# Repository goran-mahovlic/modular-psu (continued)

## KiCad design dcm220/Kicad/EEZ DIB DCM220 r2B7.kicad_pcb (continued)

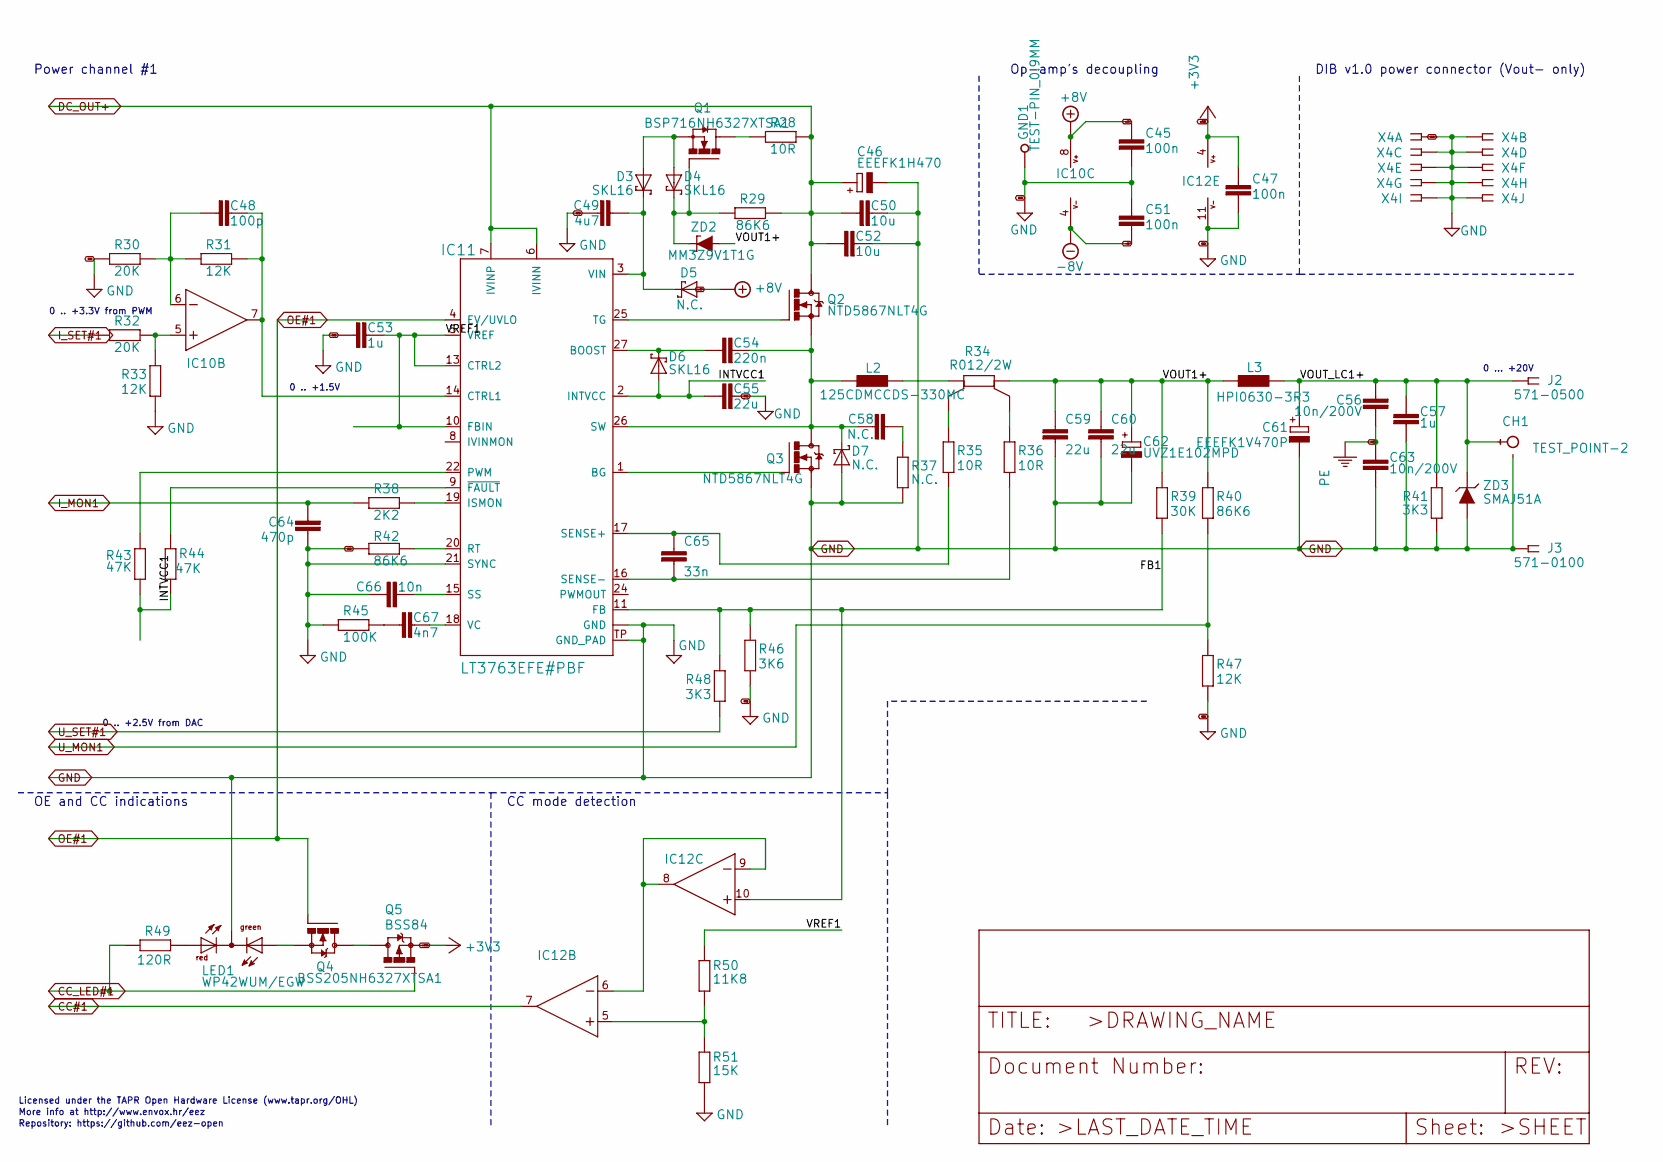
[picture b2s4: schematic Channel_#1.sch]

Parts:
C45, C47, C51: 100n; C0603
C46: EEEFK1H470; CAPAE830X1050N
C48: 100p; C0805
C49: 4u7; C1206
C50, C52: 10u; C1210
C53, C57: 1u; C0805
C54: 220n; C0805
C55: 22u; C1206
C56, C63: 10n/200V; C1206
C58: N.C.; C0805
C59, C60: 22u; C1210
C61: EEEFK1V470P; CAPAE660X610N
C62: UVZ1E102MPD; ECAP5_10.5
C64: 470p; C0805
C65: 33n; C0805
C66: 10n; C0805
C67: 4n7; C0805
CH1: TEST_POINT-2; TP_1.1MM_2
D3, D4, D6: SKL16; SOD123
D5: N.C.; SOD123
D7: N.C.; SMA
GND: TEST-PIN_0.9MM
IC10: MC33272ADR2G; SOIC127P600X173-8N
IC11: LT3763EFE#PBF; LTC_05-08-1663-EB
IC12: MC33274ADR2G; SOIC127P600X175-14N
J2: 571-0500; DELTRON_571
J3: 571-0100; DELTRON_571
L2: 125CDMCCDS-330MC; 125CDMCC_DS
L3: HPI0630-3R3; COILCRAFT_HPI0630
LED1: WP42WUM/EGW; L-42WUM-1EGWT
Q1: BSP716NH6327XTSA1; SOT223
Q2, Q3: NTD5867NLT4G; TO229P990X239-3N
Q4: BSS205NH6327XTSA1; SOT103P240X110-3N
Q5: BSS84; SOT95P237X112-3N
R28, R35, R36: 10R; R0805
R29, R40, R42: 86K6; R0805
R30, R32: 20K; R0805
R31, R33, R47: 12K; R0805
R34: R012/2W; R_2512-4WIRE
R37: N.C.; R1206
R38: 2K2; R0805
R39: 30K; R0805
R41, R48: 3K3; R0805
R43, R44: 47K; R0805
R45: 100K; R0805
R46: 3K6; R0805
R49: 120R; R0805
R50: 11K8; R0805
R51: 15K; R0805
X4: DS1024-2*5R0; SSW-105-02-T-D-RA
ZD2: MM3Z9V1T1G; SOD323-W
ZD3: SMAJ51A; DO214AA

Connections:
/Channel #1/FB1: IC11.11 (FB), IC12.10 (+IN), R39.1, R46.2, R48.2
/Channel #1/INTVCC1: C55.1, D6.A, IC11.2 (INTVCC), R43.1, R44.2
/Channel #1/VOUT1+: C59.1, C60.1, C62.+, L3.1, R34.2, R39.2, R40.2, ZD2.A
/Channel #1/VOUT_LC1+: C56.2, C57.1, C61.1 (+), CH1.TIP, J2.1, J2.1.1, L3.2, R41.1, ZD3.C
/Channel #1/VREF1: C53.1, IC11.5 (VREF), IC11.10 (FBIN), IC11.13 (CTRL2), R50.2
CC#1: IC12.7 (OUT); also elsewhere on the board
CC_LED#1: Q5.1 (G), R49.2; also elsewhere on the board
DC_OUT+: C46.+, C50.1, C52.1, IC11.6 (IVINN), IC11.7 (IVINP), Q2.2 (D), R28.1, R29.1; also elsewhere on the board
I_MON1: C64.2, R38.1; also elsewhere on the board
I_SET#1: R32.1; also elsewhere on the board
unnamed: C48.1, IC10.7 (OUT), IC11.14 (CTRL1), R31.2
unnamed: C48.2, IC10.6 (-IN), R30.2, R31.1
unnamed: C49.1, D3.C, D5.C, IC11.3 (VIN)
unnamed: C54.1, D6.C, IC11.27 (BOOST)
unnamed: C54.2, C58.1, D7.C, IC11.26 (SW), L2.1, Q2.3 (S), Q3.2 (D)
unnamed: C58.2, R37.2
unnamed: C65.1, IC11.17 (SENSE+), R35.1
unnamed: C65.2, IC11.16 (SENSE-), R36.1
unnamed: C66.2, IC11.15 (SS)
unnamed: C67.1, R45.2
unnamed: C67.2, IC11.18 (VC)
unnamed: D3.A, D4.A, Q1.3 (S)
unnamed: D4.C, Q1.1 (G), R29.2, ZD2.C
unnamed: IC10.5 (+IN), R32.2, R33.2
unnamed: IC11.1 (BG), Q3.1 (G)
unnamed: IC11.9 (~FAULT), R44.1
unnamed: IC11.19 (ISMON), R38.2
unnamed: IC11.20 (RT), R42.2
unnamed: IC11.22 (PWM), R43.2
unnamed: IC11.25 (TG), Q2.1 (G)
unnamed: IC12.5 (+IN), R50.1, R51.2
unnamed: IC12.6 (-IN), IC12.8 (OUT), IC12.9 (-IN)
unnamed: L2.2, R34.1
unnamed: LED1.GREEN (AG), Q4.2 (S)
unnamed: LED1.RED (AR), R49.1
unnamed: Q1.2 (D), Q1.4 (D), R28.2
unnamed: Q4.3 (D), Q5.3 (D)
unnamed: R34.1S, R35.2
unnamed: R34.2S, R36.2
OE#1: IC11.4 (EV/UVLO), Q4.1 (G); also elsewhere on the board
PE: C56.1, C63.1; also elsewhere on the board
U_MON1: R40.1, R47.2; also elsewhere on the board
U_SET#1: R48.1; also elsewhere on the board

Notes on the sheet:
Licensed under the TAPR Open Hardware License (www.tapr.org/OHL)
Repository: https://github.com/eez-open
More info at http://www.envox.hr/eez
0 ... +20V
0 .. +3.3V from PWM
0 .. +1.5V
0 .. +2.5V from DAC
Power channel #1
CC mode detection
DIB v1.0 power connector (Vout- only)
Op-amp's decoupling
OE and CC indications

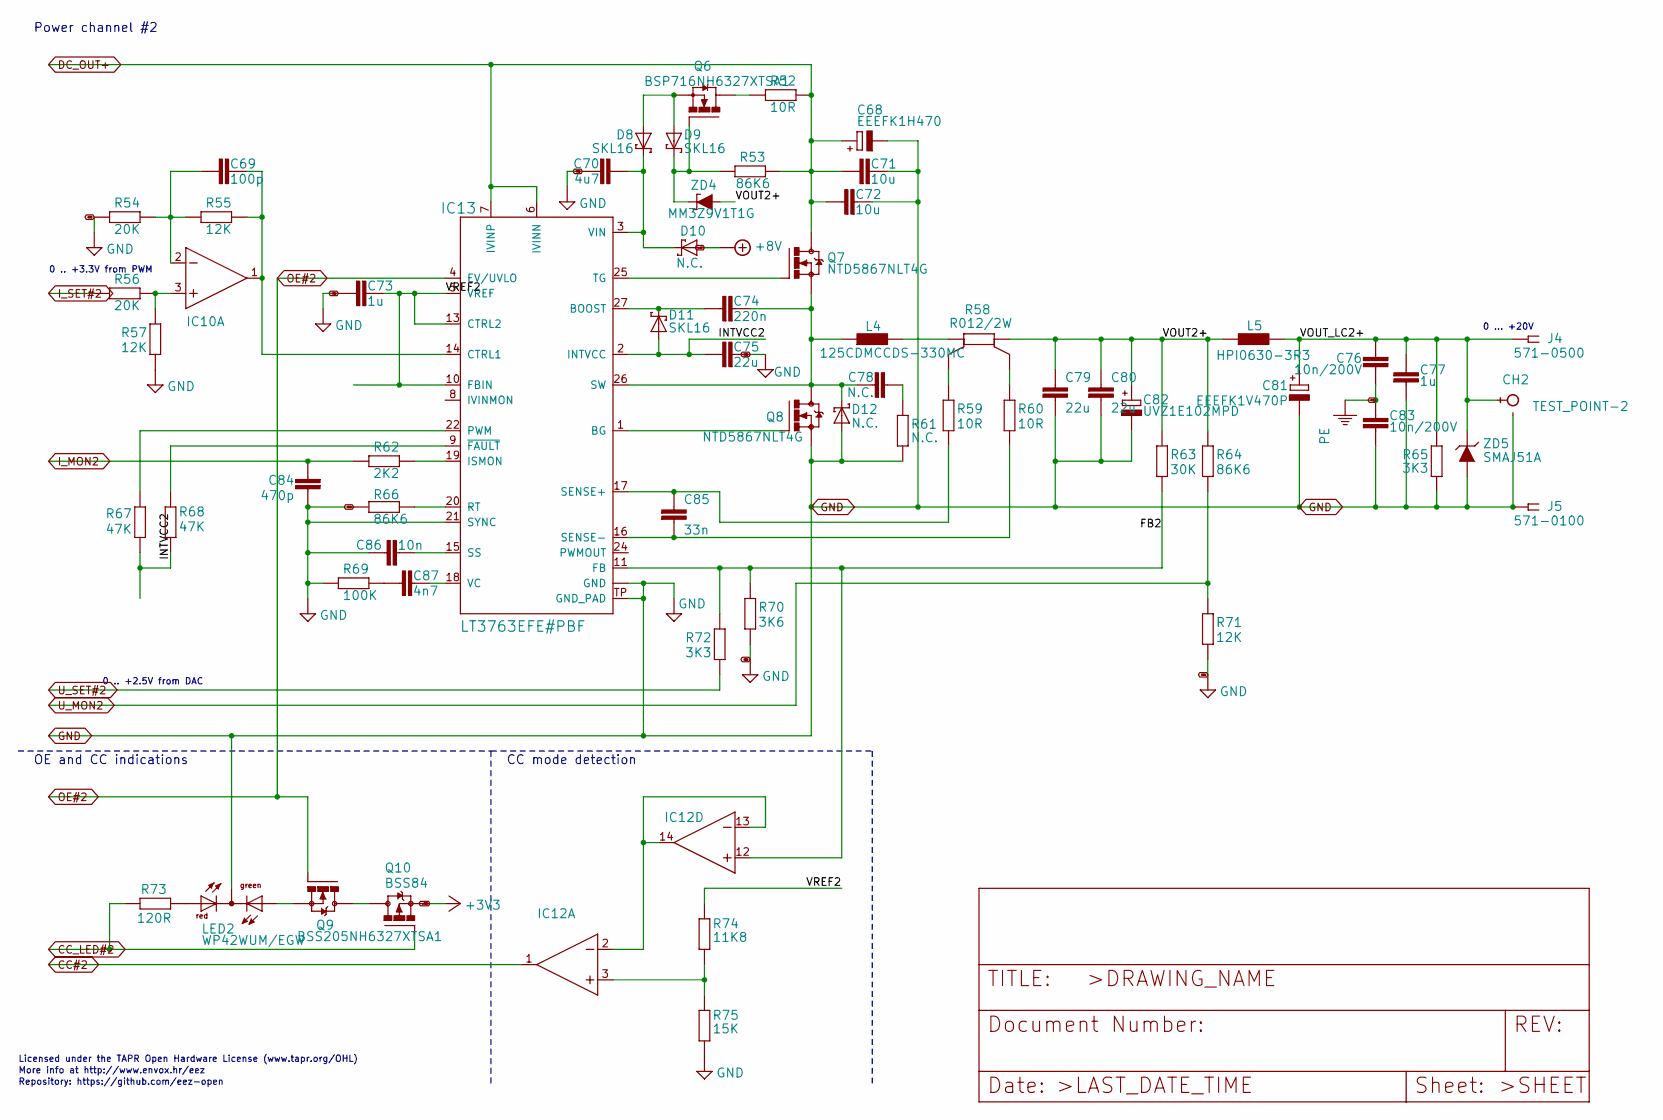
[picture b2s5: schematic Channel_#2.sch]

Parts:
C68: EEEFK1H470; CAPAE830X1050N
C69: 100p; C0805
C70: 4u7; C1206
C71, C72: 10u; C1210
C73, C77: 1u; C0805
C74: 220n; C0805
C75: 22u; C1206
C76, C83: 10n/200V; C1206
C78: N.C.; C0805
C79, C80: 22u; C1210
C81: EEEFK1V470P; CAPAE660X610N
C82: UVZ1E102MPD; ECAP5_10.5
C84: 470p; C0805
C85: 33n; C0805
C86: 10n; C0805
C87: 4n7; C0805
CH2: TEST_POINT-2; TP_1.1MM_2
D8, D9, D11: SKL16; SOD123
D10: N.C.; SOD123
D12: N.C.; SMA
IC10: MC33272ADR2G; SOIC127P600X173-8N
IC12: MC33274ADR2G; SOIC127P600X175-14N
IC13: LT3763EFE#PBF; LTC_05-08-1663-EB
J4: 571-0500; DELTRON_571
J5: 571-0100; DELTRON_571
L4: 125CDMCCDS-330MC; 125CDMCC_DS
L5: HPI0630-3R3; COILCRAFT_HPI0630
LED2: WP42WUM/EGW; L-42WUM-1EGWT
Q6: BSP716NH6327XTSA1; SOT223
Q7, Q8: NTD5867NLT4G; TO229P990X239-3N
Q9: BSS205NH6327XTSA1; SOT103P240X110-3N
Q10: BSS84; SOT95P237X112-3N
R52, R59, R60: 10R; R0805
R53, R64, R66: 86K6; R0805
R54, R56: 20K; R0805
R55, R57, R71: 12K; R0805
R58: R012/2W; R_2512-4WIRE
R61: N.C.; R1206
R62: 2K2; R0805
R63: 30K; R0805
R65, R72: 3K3; R0805
R67, R68: 47K; R0805
R69: 100K; R0805
R70: 3K6; R0805
R73: 120R; R0805
R74: 11K8; R0805
R75: 15K; R0805
ZD4: MM3Z9V1T1G; SOD323-W
ZD5: SMAJ51A; DO214AA

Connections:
/Channel #2/FB2: IC12.12 (+IN), IC13.11 (FB), R63.1, R70.2, R72.2
/Channel #2/INTVCC2: C75.1, D11.A, IC13.2 (INTVCC), R67.1, R68.2
/Channel #2/VOUT2+: C79.1, C80.1, C82.+, L5.1, R58.2, R63.2, R64.2, ZD4.A
/Channel #2/VOUT_LC2+: C76.2, C77.1, C81.1 (+), CH2.TIP, J4.1, J4.1.1, L5.2, R65.1, ZD5.C
/Channel #2/VREF2: C73.1, IC13.5 (VREF), IC13.10 (FBIN), IC13.13 (CTRL2), R74.2
CC#2: IC12.1 (OUT); also elsewhere on the board
CC_LED#2: Q10.1 (G), R73.2; also elsewhere on the board
DC_OUT+: C68.+, C71.1, C72.1, IC13.6 (IVINN), IC13.7 (IVINP), Q7.2 (D), R52.1, R53.1; also elsewhere on the board
I_MON2: C84.2, R62.1; also elsewhere on the board
I_SET#2: R56.1; also elsewhere on the board
unnamed: C69.1, IC10.1 (OUT), IC13.14 (CTRL1), R55.2
unnamed: C69.2, IC10.2 (-IN), R54.2, R55.1
unnamed: C70.1, D8.C, D10.C, IC13.3 (VIN)
unnamed: C74.1, D11.C, IC13.27 (BOOST)
unnamed: C74.2, C78.1, D12.C, IC13.26 (SW), L4.1, Q7.3 (S), Q8.2 (D)
unnamed: C78.2, R61.2
unnamed: C85.1, IC13.17 (SENSE+), R59.1
unnamed: C85.2, IC13.16 (SENSE-), R60.1
unnamed: C86.2, IC13.15 (SS)
unnamed: C87.1, R69.2
unnamed: C87.2, IC13.18 (VC)
unnamed: D8.A, D9.A, Q6.3 (S)
unnamed: D9.C, Q6.1 (G), R53.2, ZD4.C
unnamed: IC10.3 (+IN), R56.2, R57.2
unnamed: IC12.3 (+IN), R74.1, R75.2
unnamed: IC12.2 (-IN), IC12.13 (-IN), IC12.14 (OUT)
unnamed: IC13.1 (BG), Q8.1 (G)
unnamed: IC13.9 (~FAULT), R68.1
unnamed: IC13.19 (ISMON), R62.2
unnamed: IC13.20 (RT), R66.2
unnamed: IC13.22 (PWM), R67.2
unnamed: IC13.25 (TG), Q7.1 (G)
unnamed: L4.2, R58.1
unnamed: LED2.GREEN (AG), Q9.2 (S)
unnamed: LED2.RED (AR), R73.1
unnamed: Q6.2 (D), Q6.4 (D), R52.2
unnamed: Q9.3 (D), Q10.3 (D)
unnamed: R58.1S, R59.2
unnamed: R58.2S, R60.2
OE#2: IC13.4 (EV/UVLO), Q9.1 (G); also elsewhere on the board
PE: C76.1, C83.1; also elsewhere on the board
U_MON2: R64.1, R71.2; also elsewhere on the board
U_SET#2: R72.1; also elsewhere on the board

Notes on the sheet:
Licensed under the TAPR Open Hardware License (www.tapr.org/OHL)
Repository: https://github.com/eez-open
More info at http://www.envox.hr/eez
0 ... +20V
CC mode detection
OE and CC indications
Power channel #2
0 .. +3.3V from PWM
0 .. +2.5V from DAC

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
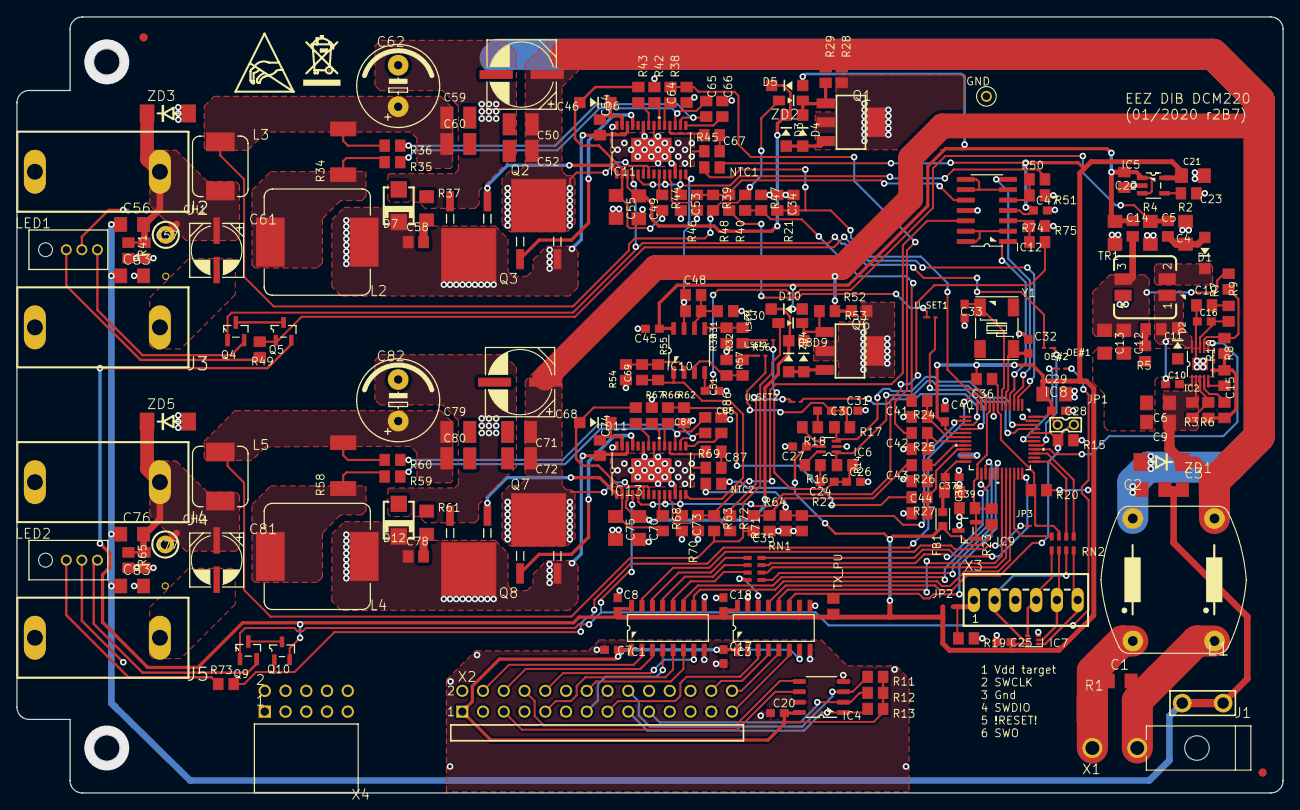
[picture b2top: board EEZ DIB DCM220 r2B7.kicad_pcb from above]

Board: 2 copper layers, 155.0 x 95.0 mm, 247 parts (0 on the bottom side), 168 nets.

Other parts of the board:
EEZ_SIGNATURE: SIGNATURESMALL; SIGNATURE_5MM
U$2: RECYCLE_BIN1_8
U$4: ESD_SYMBOL

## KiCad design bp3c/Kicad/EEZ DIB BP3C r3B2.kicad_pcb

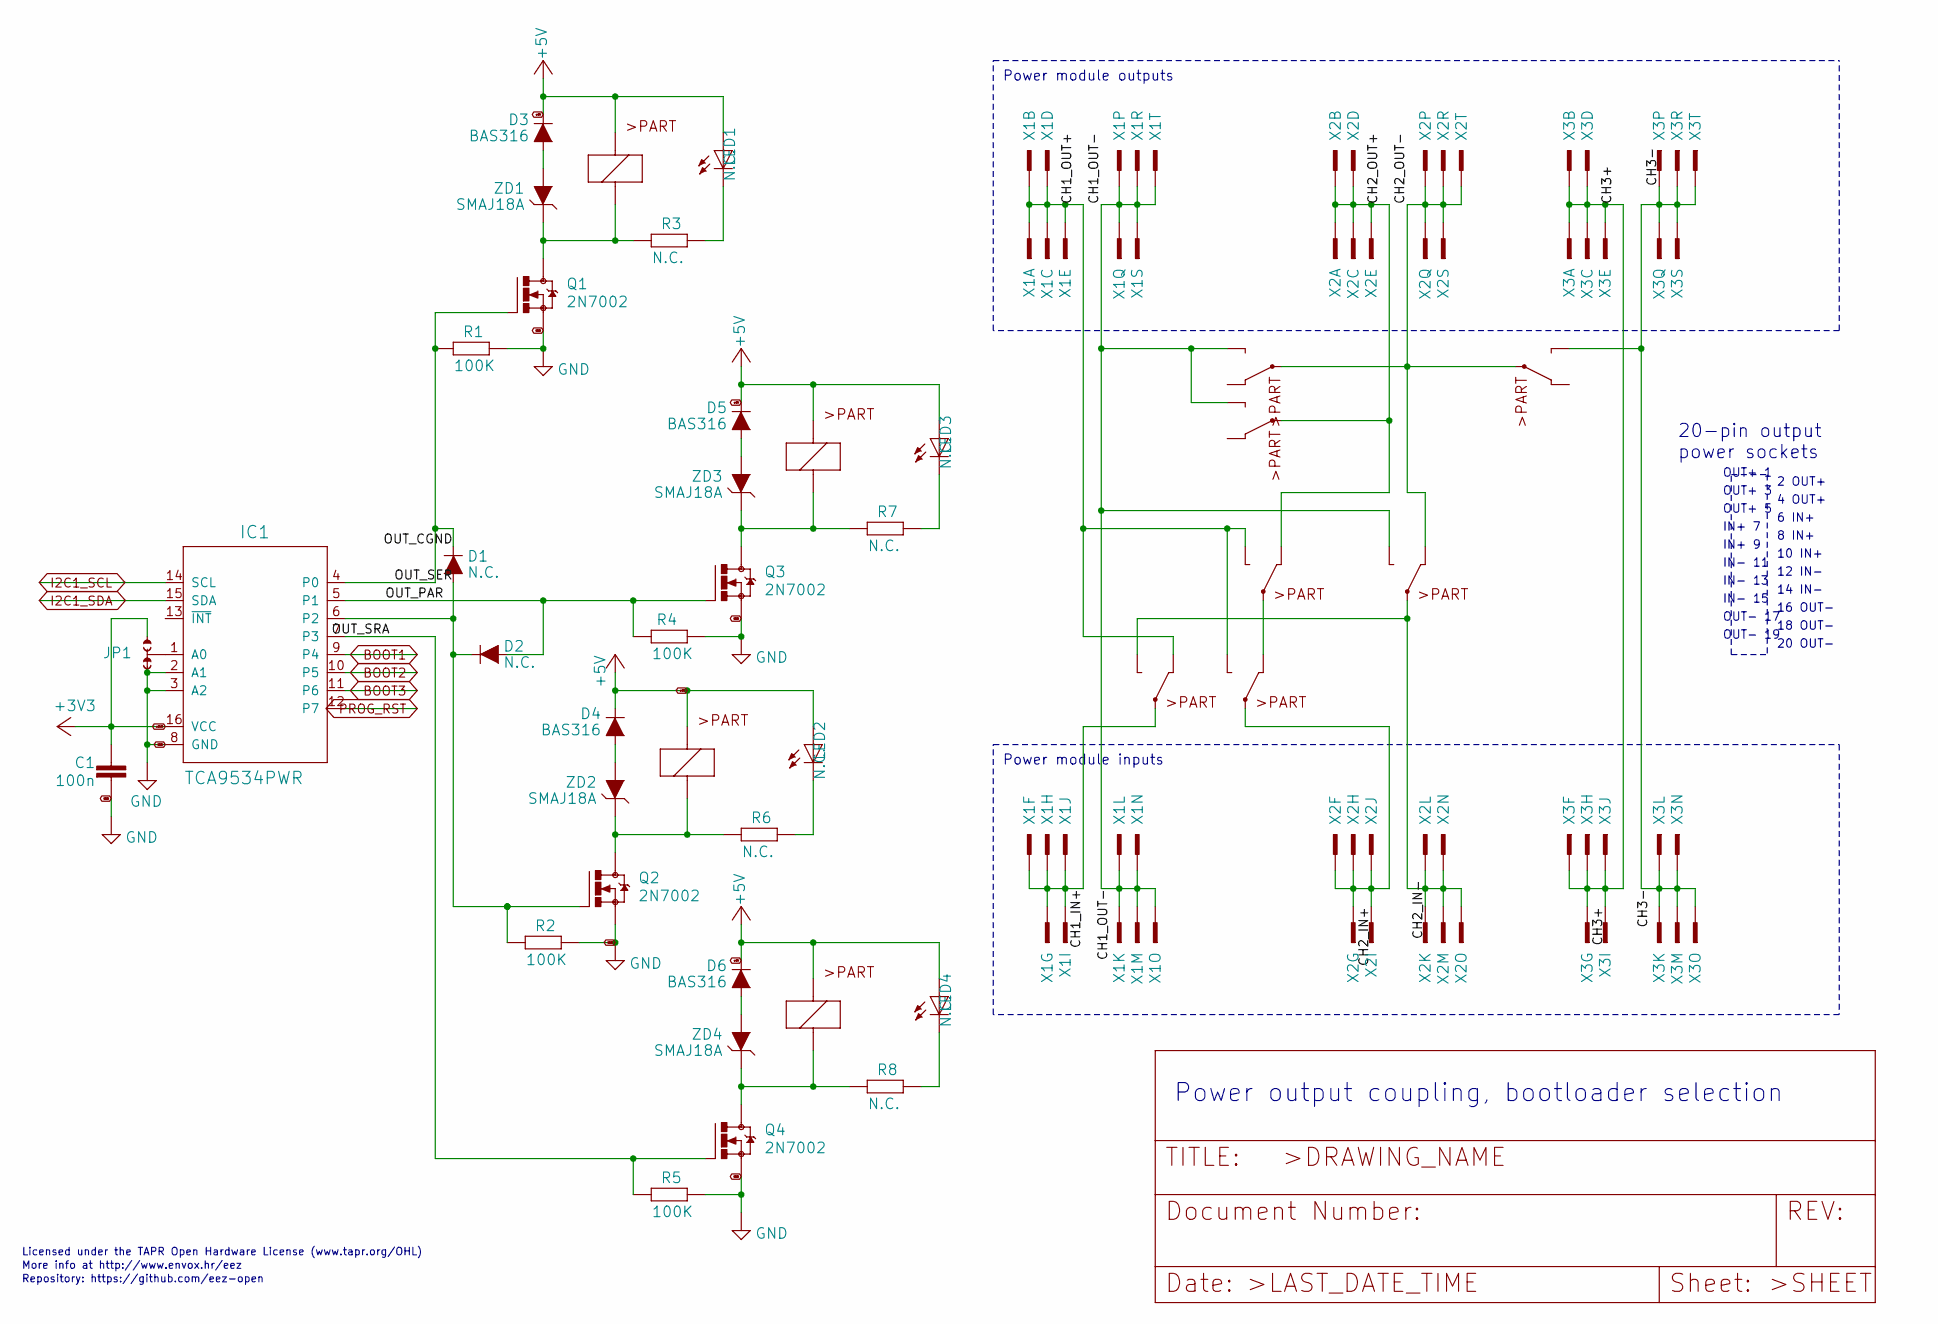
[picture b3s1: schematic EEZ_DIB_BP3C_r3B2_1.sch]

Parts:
C1: 100n; C0603
D1, D2: N.C.; SOD323-R
D3, D4, D5, D6: BAS316; SOD323-R
IC1: TCA9534PWR; PW(R-PDSO-G16)
JP1: JP3-CUT
K1, K2, K3, K4: RT424005; RT-C_016A5_ROUND
LED1, LED2, LED3, LED4: N.C.; LED_0805
Q1, Q2, Q3, Q4: 2N7002; SOT103P240X110-3N
R1, R2, R4, R5: 100K; R0805
R3, R6, R7, R8: N.C.; R0805
X1, X2, X3: ZL202-20G; DS1021-2*10SF11
ZD1, ZD2, ZD3, ZD4: SMAJ18A; DO214AC

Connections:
+3V3: C1.1, IC1.16 (VCC), JP1.NO; also elsewhere on the board
+5V: D3.C, D4.C, D5.C, D6.C, K1.A2 (C1), K2.A2 (C1), K3.A2 (C1), K4.A2 (C1), LED1.A, LED2.A, LED3.A, LED4.A; also elsewhere on the board
/EEZ DIB BP3C r3B2_1/CH1_IN+: K1.11A, X1.6, X1.7, X1.8, X1.9, X1.10
/EEZ DIB BP3C r3B2_1/CH1_OUT+: K1.12A (S), K1.14B (O), K2.14A (O), X1.1, X1.2, X1.3, X1.4, X1.5
/EEZ DIB BP3C r3B2_1/CH1_OUT-: K2.14B (O), K3.14A (O), K4.14A (O), X1.11, X1.12, X1.13, X1.14, X1.15, X1.16, X1.17, X1.18, X1.19, X1.20
/EEZ DIB BP3C r3B2_1/CH2_IN+: K1.11B, X2.6, X2.7, X2.8, X2.9, X2.10
/EEZ DIB BP3C r3B2_1/CH2_IN-: K1.14A (O), K2.11B, X2.11, X2.12, X2.13, X2.14, X2.15
/EEZ DIB BP3C r3B2_1/CH2_OUT+: K2.12A (S), K4.11A, X2.1, X2.2, X2.3, X2.4, X2.5
/EEZ DIB BP3C r3B2_1/CH2_OUT-: K2.12B (S), K3.11A, K3.11B, X2.16, X2.17, X2.18, X2.19, X2.20
/EEZ DIB BP3C r3B2_1/CH3+: X3.1, X3.2, X3.3, X3.4, X3.5, X3.6, X3.7, X3.8, X3.9, X3.10
/EEZ DIB BP3C r3B2_1/CH3-: K3.14B (O), X3.11, X3.12, X3.13, X3.14, X3.15, X3.16, X3.17, X3.18, X3.19, X3.20
/EEZ DIB BP3C r3B2_1/OUT_CGND: D1.C, IC1.4 (P0), Q1.1 (G), R1.2
/EEZ DIB BP3C r3B2_1/OUT_PAR: D2.A, IC1.5 (P1), Q3.1 (G), R4.2
/EEZ DIB BP3C r3B2_1/OUT_SER: D1.A, D2.C, IC1.6 (P2), Q2.1 (G), R2.2
/EEZ DIB BP3C r3B2_1/OUT_SRA: IC1.7 (P3), Q4.1 (G), R5.2
BOOT1: IC1.9 (P4); also elsewhere on the board
BOOT2: IC1.10 (P5); also elsewhere on the board
BOOT3: IC1.11 (P6); also elsewhere on the board
GND: C1.2, IC1.2 (A1), IC1.3 (A2), IC1.8 (GND), JP1.NC, Q1.2 (S), Q2.2 (S), Q3.2 (S), Q4.2 (S), R1.1, R2.1, R4.1, R5.1; also elsewhere on the board
I2C1_SCL: IC1.14 (SCL); also elsewhere on the board
I2C1_SDA: IC1.15 (SDA); also elsewhere on the board
unnamed: D3.A, ZD1.A
unnamed: D4.A, ZD2.A
unnamed: D5.A, ZD3.A
unnamed: D6.A, ZD4.A
unnamed: IC1.1 (A0), JP1.COM
unnamed: K1.12B (S), K2.11A
unnamed: K1.A1 (C2), Q2.3 (D), R6.2, ZD2.C
unnamed: K2.A1 (C2), Q3.3 (D), R7.2, ZD3.C
unnamed: K3.A1 (C2), Q1.3 (D), R3.2, ZD1.C
unnamed: K4.A1 (C2), Q4.3 (D), R8.2, ZD4.C
unnamed: LED1.C, R3.1
unnamed: LED2.C, R6.1
unnamed: LED3.C, R7.1
unnamed: LED4.C, R8.1
PROG_RST: IC1.12 (P7); also elsewhere on the board

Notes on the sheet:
Licensed under the TAPR Open Hardware License (www.tapr.org/OHL)
Repository: https://github.com/eez-open
More info at http://www.envox.hr/eez
Power output coupling, bootloader selection
Power module inputs
Power module outputs
IN+ 7
16 OUT-
6 IN+
20-pin output power sockets
10 IN+
IN+ 9
2 OUT+
12 IN-
OUT+ 1
IN- 11
8 IN+
OUT+ 5
OUT- 19
4 OUT+
OUT- 17
20 OUT-
OUT+ 3
14 IN-
IN- 15
IN- 13
18 OUT-

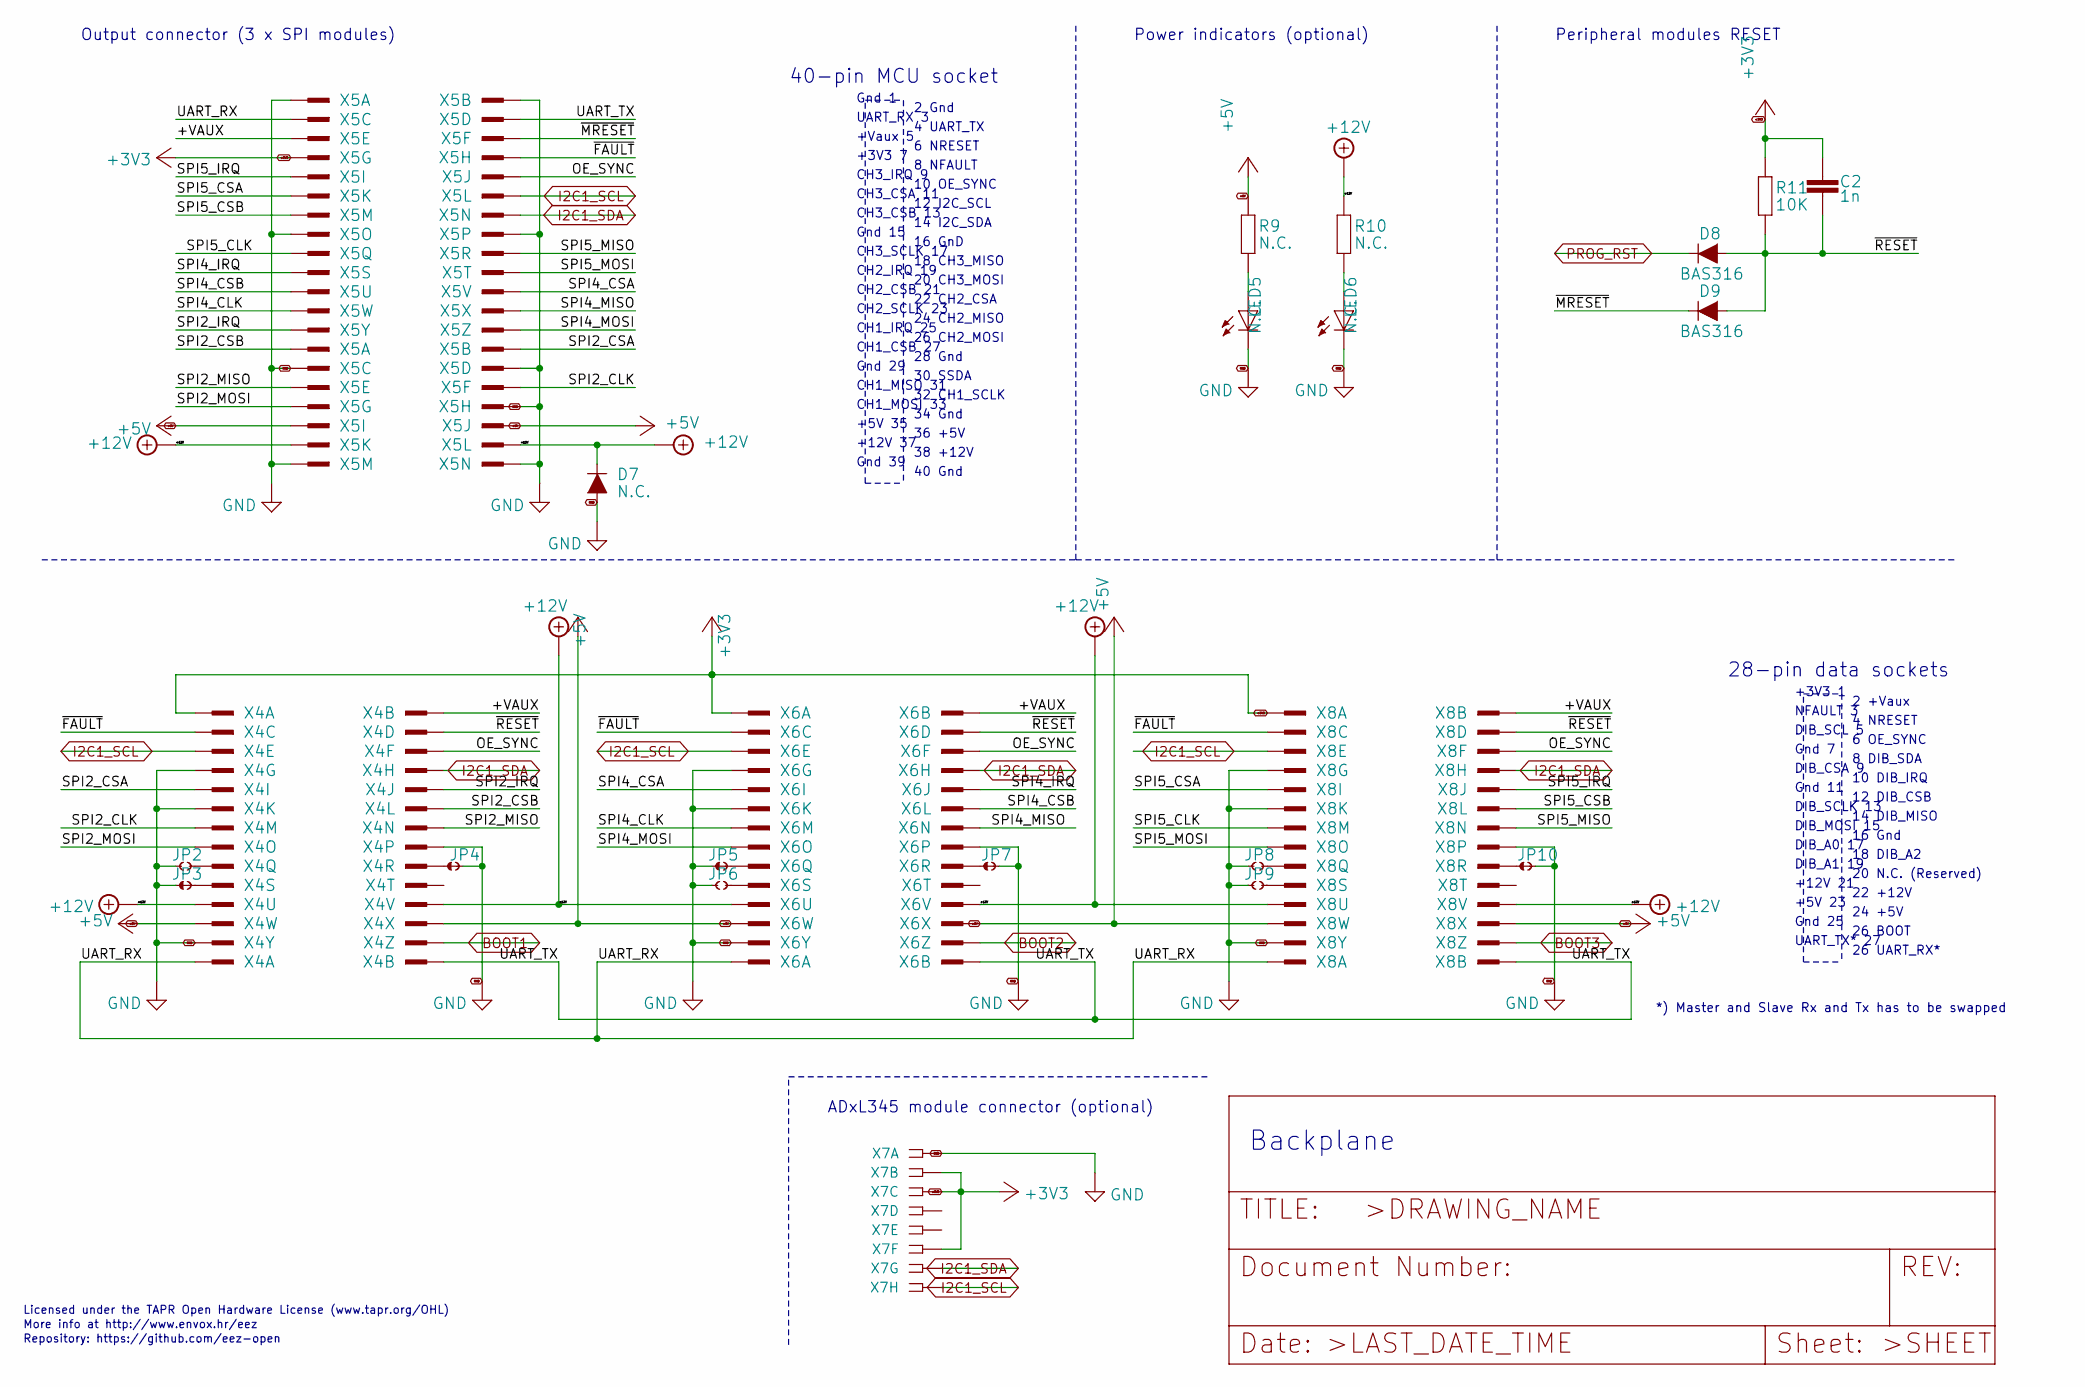
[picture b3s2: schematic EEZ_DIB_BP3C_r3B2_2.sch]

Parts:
C2: 1n; C0805
D7: N.C.; DO214AA
D8, D9: BAS316; SOD323-R
JP2, JP6, JP8, JP9: JP2-CUT
JP3, JP4, JP5, JP7, JP10: JP2-NOCUT
LED5, LED6: N.C.; LED_0805
R9, R10: N.C.; R0805
R11: 10K; R0805
X4, X6, X8: DS1023-2*14S21; TSW-114-07-F-D
X5: DS1022-2*20RF11; ZL212-40KG
X7: N.C.; SSW-108-02-S-S

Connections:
+3V3: C2.2, R11.1, X4.1, X5.7, X6.1, X7.2, X7.3, X7.6, X8.1; also elsewhere on the board
+5V: R9.1, X4.23, X4.24, X5.35, X5.36, X6.23, X6.24, X8.23, X8.24; also elsewhere on the board
+12V: D7.C, R10.1, X4.21, X4.22, X5.37, X5.38, X6.21, X6.22, X8.21, X8.22
/EEZ DIB BP3C r3B2_2/+VAUX: X4.2, X5.5, X6.2, X8.2
/EEZ DIB BP3C r3B2_2/OE_SYNC: X4.6, X5.10, X6.6, X8.6
/EEZ DIB BP3C r3B2_2/SPI2_CLK: X4.13, X5.32
/EEZ DIB BP3C r3B2_2/SPI2_CSA: X4.9, X5.28
/EEZ DIB BP3C r3B2_2/SPI2_CSB: X4.12, X5.27
/EEZ DIB BP3C r3B2_2/SPI2_IRQ: X4.10, X5.25
/EEZ DIB BP3C r3B2_2/SPI2_MISO: X4.14, X5.31
/EEZ DIB BP3C r3B2_2/SPI2_MOSI: X4.15, X5.33
/EEZ DIB BP3C r3B2_2/SPI4_CLK: X5.23, X6.13
/EEZ DIB BP3C r3B2_2/SPI4_CSA: X5.22, X6.9
/EEZ DIB BP3C r3B2_2/SPI4_CSB: X5.21, X6.12
/EEZ DIB BP3C r3B2_2/SPI4_IRQ: X5.19, X6.10
/EEZ DIB BP3C r3B2_2/SPI4_MISO: X5.24, X6.14
/EEZ DIB BP3C r3B2_2/SPI4_MOSI: X5.26, X6.15
/EEZ DIB BP3C r3B2_2/SPI5_CLK: X5.17, X8.13
/EEZ DIB BP3C r3B2_2/SPI5_CSA: X5.11, X8.9
/EEZ DIB BP3C r3B2_2/SPI5_CSB: X5.13, X8.12
/EEZ DIB BP3C r3B2_2/SPI5_IRQ: X5.9, X8.10
/EEZ DIB BP3C r3B2_2/SPI5_MISO: X5.18, X8.14
/EEZ DIB BP3C r3B2_2/SPI5_MOSI: X5.20, X8.15
/EEZ DIB BP3C r3B2_2/UART_RX: X4.27, X5.3, X6.27, X8.27
/EEZ DIB BP3C r3B2_2/UART_TX: X4.28, X5.4, X6.28, X8.28
/EEZ DIB BP3C r3B2_2/~FAULT: X4.3, X5.8, X6.3, X8.3
/EEZ DIB BP3C r3B2_2/~MRESET: D9.C, X5.6
/EEZ DIB BP3C r3B2_2/~RESET: C2.1, D8.A, D9.A, R11.2, X4.4, X6.4, X8.4
BOOT1: X4.26; also elsewhere on the board
BOOT2: X6.26; also elsewhere on the board
BOOT3: X8.26; also elsewhere on the board
GND: D7.A, JP2.1, JP3.1, JP4.2, JP5.1, JP6.1, JP7.2, JP8.1, JP9.1, JP10.2, LED5.C, LED6.C, X4.7, X4.11, X4.16, X4.25, X5.1, X5.2, X5.15, X5.16, X5.29, X5.30, X5.34, X5.39, X5.40, X6.7, X6.11, X6.16, X6.25, X7.1, X8.7, X8.11, X8.16, X8.25; also elsewhere on the board
I2C1_SCL: X4.5, X5.12, X6.5, X7.8, X8.5; also elsewhere on the board
I2C1_SDA: X4.8, X5.14, X6.8, X7.7, X8.8; also elsewhere on the board
unnamed: JP2.2, X4.17
unnamed: JP3.2, X4.19
unnamed: JP4.1, X4.18
unnamed: JP5.2, X6.17
unnamed: JP6.2, X6.19
unnamed: JP7.1, X6.18
unnamed: JP8.2, X8.17
unnamed: JP9.2, X8.19
unnamed: JP10.1, X8.18
unnamed: LED5.A, R9.2
unnamed: LED6.A, R10.2
PROG_RST: D8.C; also elsewhere on the board

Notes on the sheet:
Licensed under the TAPR Open Hardware License (www.tapr.org/OHL)
Repository: https://github.com/eez-open
More info at http://www.envox.hr/eez
Backplane
2 Gnd
+3V3 7
6 NRESET
8 NFAULT
10 OE_SYNC
4 UART_TX
UART_RX 3
Gnd 1
40-pin MCU socket
+Vaux 5
CH3_IRQ 9
CH3_CSB 13
12 I2C_SCL
CH3_CSA 11
14 I2C_SDA
Gnd 15
16 GnD
18 CH3_MISO
CH2_SCLK 23
22 CH2_CSA
24 CH2_MISO
26 CH2_MOSI
20 CH3_MOSI
CH2_IRQ 19
CH3_SCLK 17
CH2_CSB 21
CH1_IRQ 25
Gnd 29
28 Gnd
CH1_CSB 27
30 SSDA
CH1_MISO 31
32 CH1_SCLK
CH1_MOSI 33
+12V 37
+5V 35

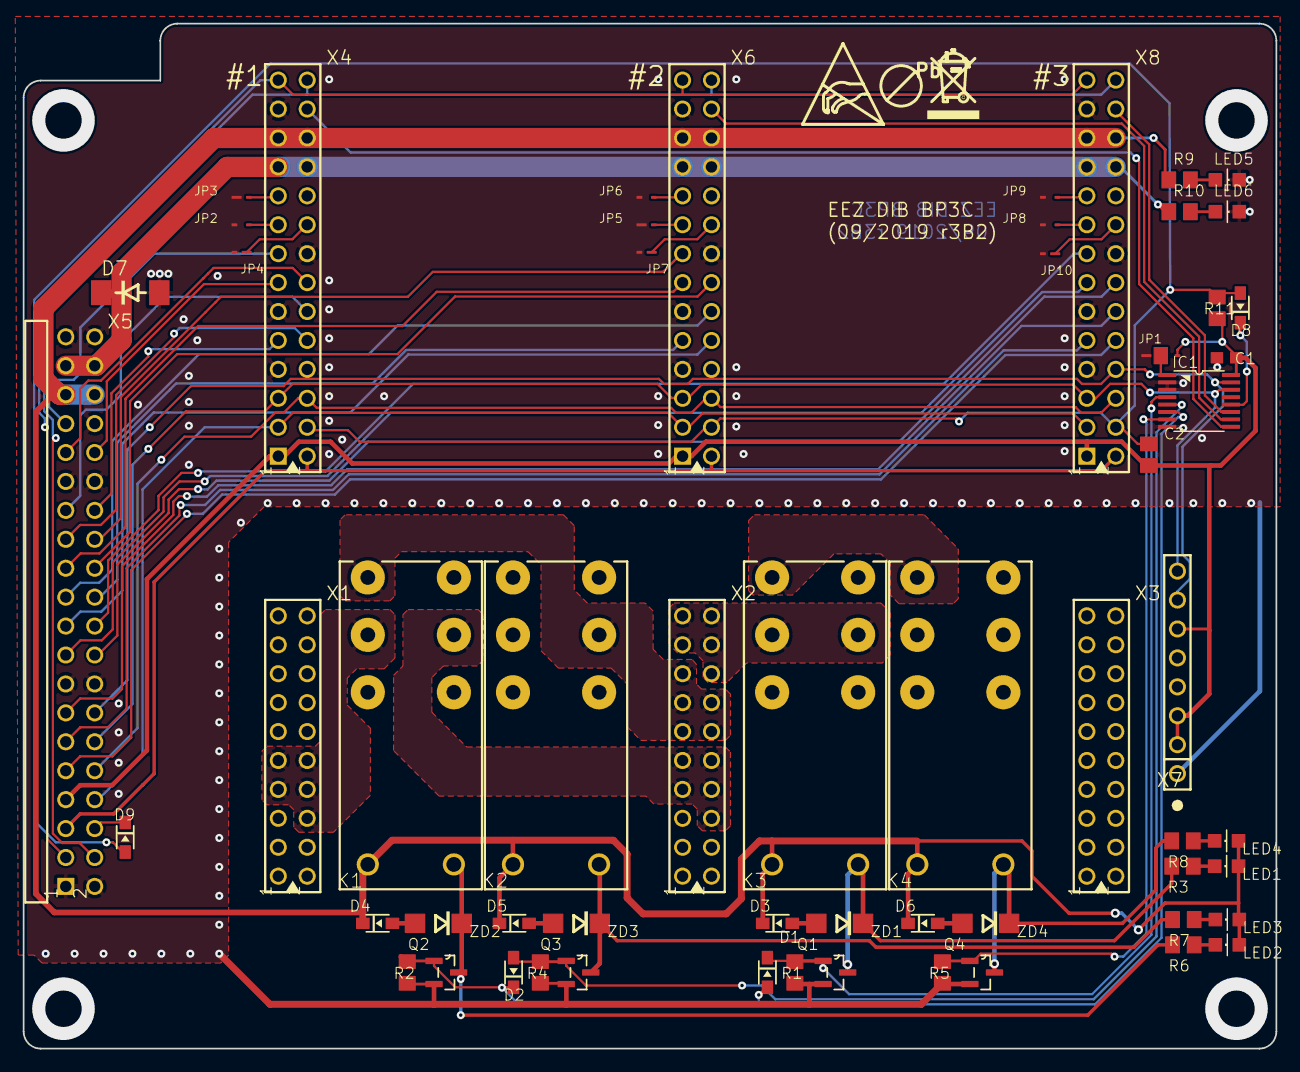
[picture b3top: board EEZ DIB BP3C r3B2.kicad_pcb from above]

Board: 2 copper layers, 110.0 x 90.0 mm, 63 parts (0 on the bottom side), 73 nets.

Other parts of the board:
EEZ_SIGNATURE: SIGNATURESMALL; SIGNATURE_5MM
U$2: RECYCLE_BIN1_8
U$4: ESD_SYMBOL
U$5: PB_SMALL
